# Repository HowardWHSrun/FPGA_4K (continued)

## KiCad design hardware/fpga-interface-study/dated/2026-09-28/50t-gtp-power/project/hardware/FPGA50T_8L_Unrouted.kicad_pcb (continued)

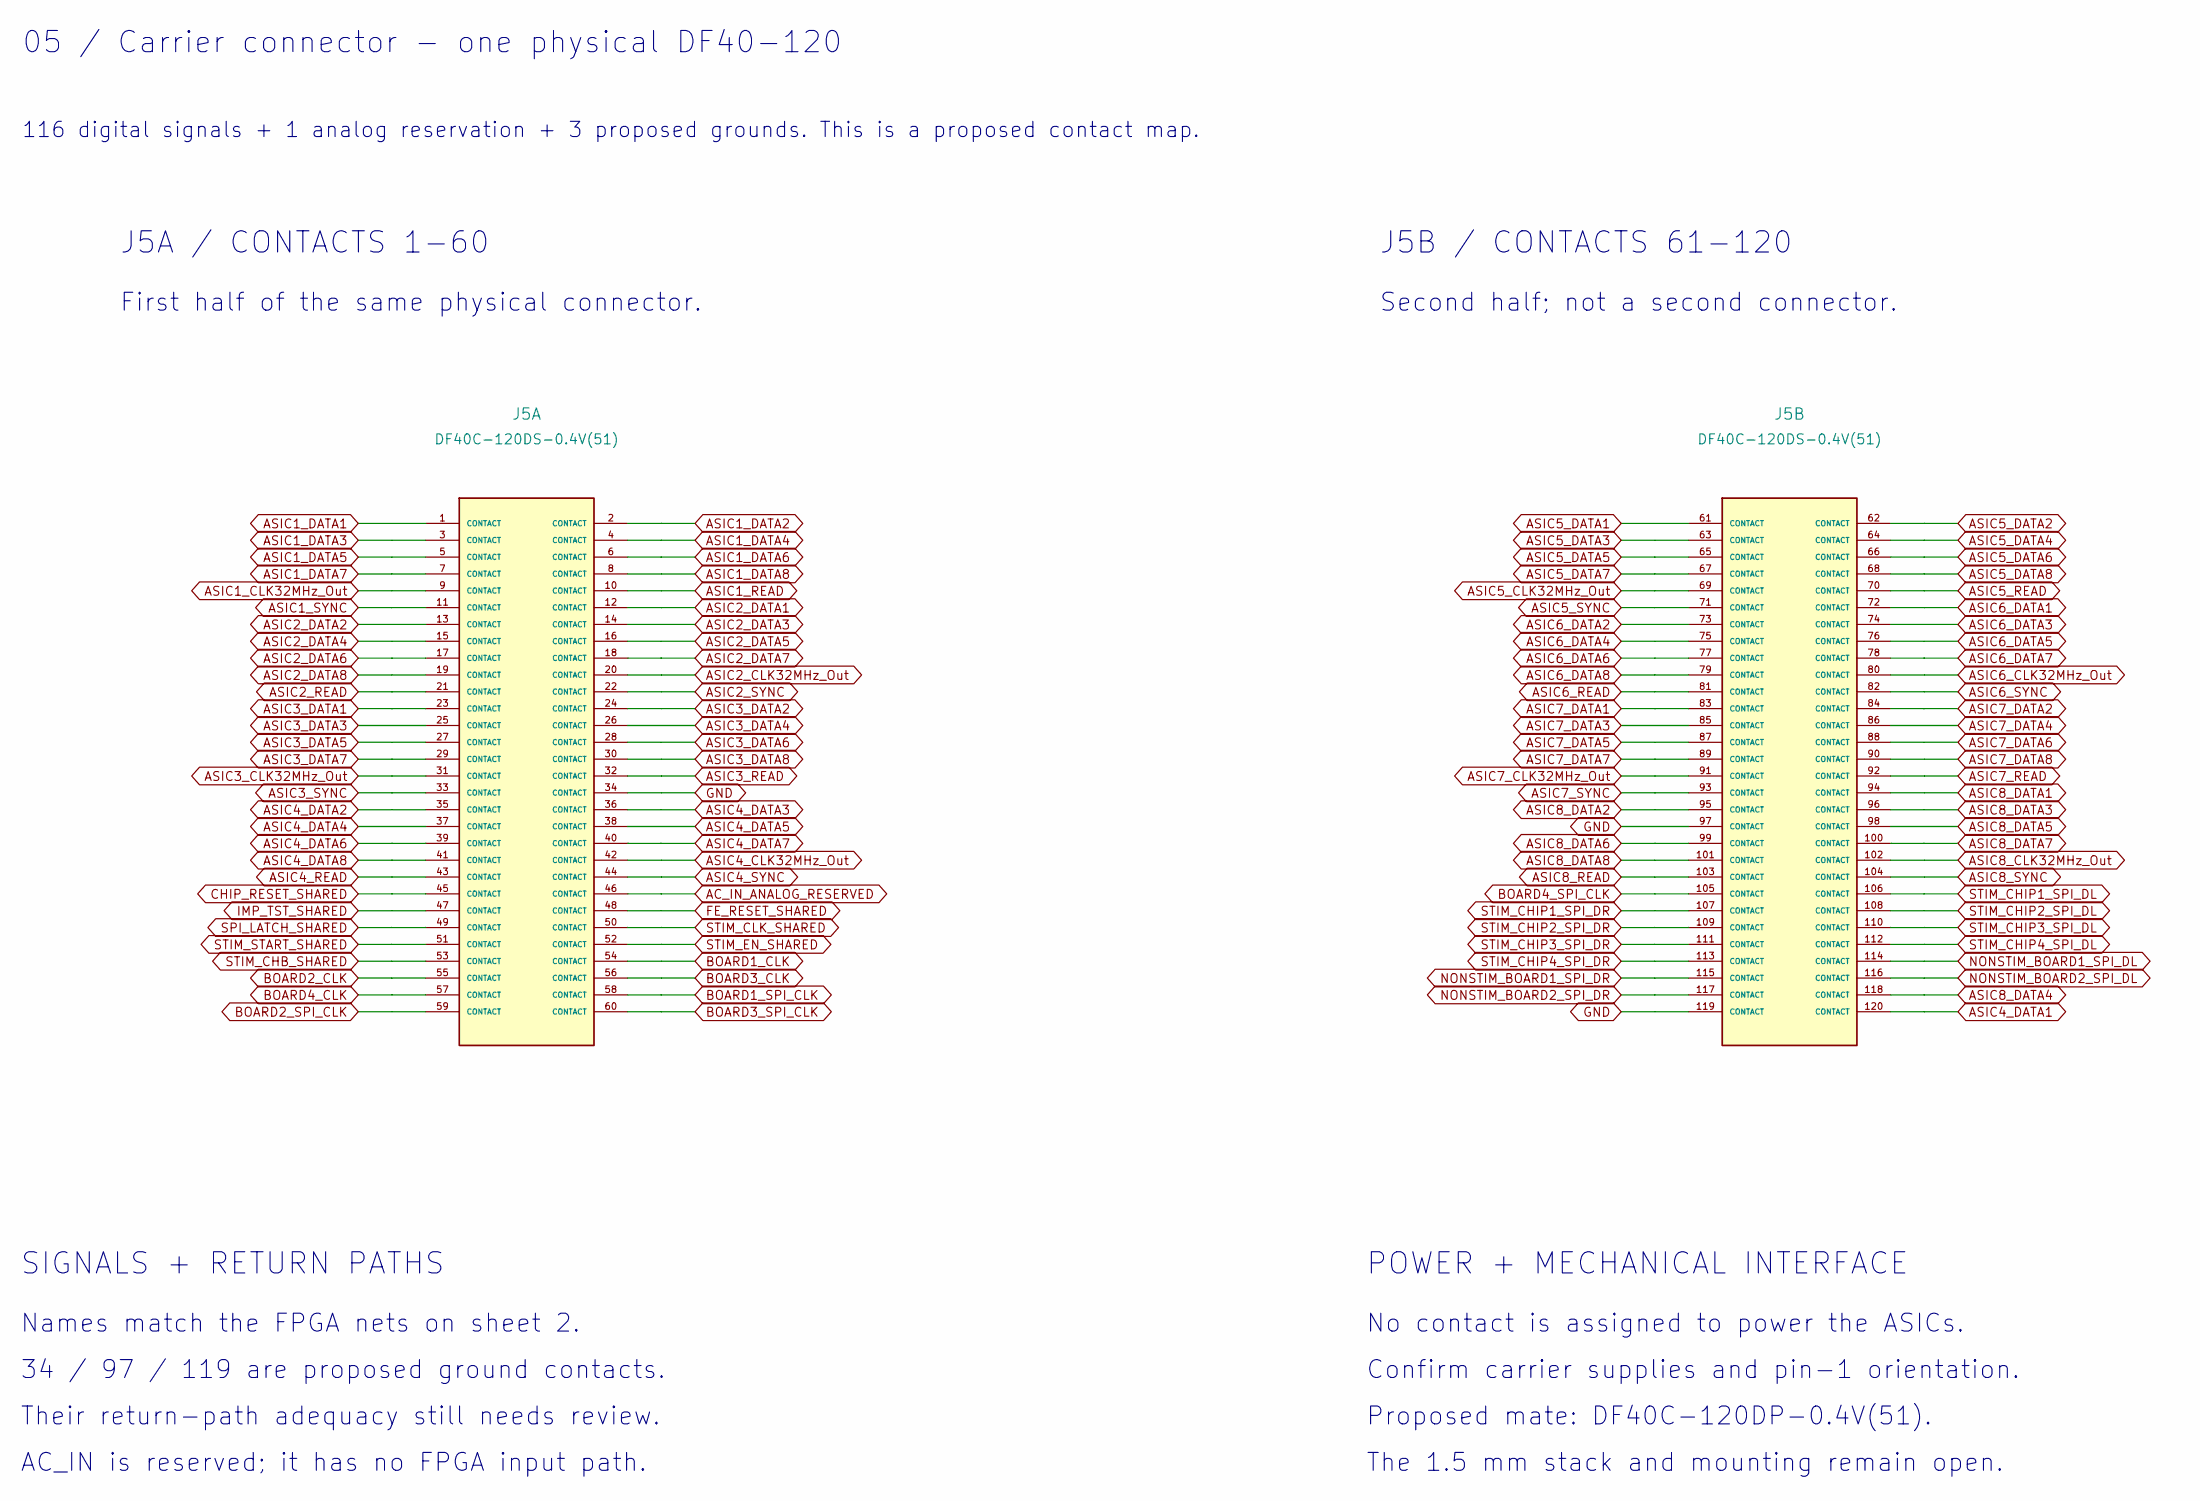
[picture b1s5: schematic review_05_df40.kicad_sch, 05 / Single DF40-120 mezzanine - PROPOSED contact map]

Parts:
J5: DF40C-120DS-0.4V(51); Hirose_DF40C-120DS-0.4V_2x60_P0.4mm; MPN DF40C-120DS-0.4V(51)

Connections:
AC_IN_ANALOG_RESERVED: J5.46
ASIC1_CLK32MHz_Out: J5.9; also elsewhere on the board
ASIC1_DATA1: J5.1; also elsewhere on the board
ASIC1_DATA2: J5.2; also elsewhere on the board
ASIC1_DATA3: J5.3; also elsewhere on the board
ASIC1_DATA4: J5.4; also elsewhere on the board
ASIC1_DATA5: J5.5; also elsewhere on the board
ASIC1_DATA6: J5.6; also elsewhere on the board
ASIC1_DATA7: J5.7; also elsewhere on the board
ASIC1_DATA8: J5.8; also elsewhere on the board
ASIC1_READ: J5.10; also elsewhere on the board
ASIC1_SYNC: J5.11; also elsewhere on the board
ASIC2_CLK32MHz_Out: J5.20; also elsewhere on the board
ASIC2_DATA1: J5.12; also elsewhere on the board
ASIC2_DATA2: J5.13; also elsewhere on the board
ASIC2_DATA3: J5.14; also elsewhere on the board
ASIC2_DATA4: J5.15; also elsewhere on the board
ASIC2_DATA5: J5.16; also elsewhere on the board
ASIC2_DATA6: J5.17; also elsewhere on the board
ASIC2_DATA7: J5.18; also elsewhere on the board
ASIC2_DATA8: J5.19; also elsewhere on the board
ASIC2_READ: J5.21; also elsewhere on the board
ASIC2_SYNC: J5.22; also elsewhere on the board
ASIC3_CLK32MHz_Out: J5.31; also elsewhere on the board
ASIC3_DATA1: J5.23; also elsewhere on the board
ASIC3_DATA2: J5.24; also elsewhere on the board
ASIC3_DATA3: J5.25; also elsewhere on the board
ASIC3_DATA4: J5.26; also elsewhere on the board
ASIC3_DATA5: J5.27; also elsewhere on the board
ASIC3_DATA6: J5.28; also elsewhere on the board
ASIC3_DATA7: J5.29; also elsewhere on the board
ASIC3_DATA8: J5.30; also elsewhere on the board
ASIC3_READ: J5.32; also elsewhere on the board
ASIC3_SYNC: J5.33; also elsewhere on the board
ASIC4_CLK32MHz_Out: J5.42; also elsewhere on the board
ASIC4_DATA1: J5.120; also elsewhere on the board
ASIC4_DATA2: J5.35; also elsewhere on the board
ASIC4_DATA3: J5.36; also elsewhere on the board
ASIC4_DATA4: J5.37; also elsewhere on the board
ASIC4_DATA5: J5.38; also elsewhere on the board
ASIC4_DATA6: J5.39; also elsewhere on the board
ASIC4_DATA7: J5.40; also elsewhere on the board
ASIC4_DATA8: J5.41; also elsewhere on the board
ASIC4_READ: J5.43; also elsewhere on the board
ASIC4_SYNC: J5.44; also elsewhere on the board
ASIC5_CLK32MHz_Out: J5.69; also elsewhere on the board
ASIC5_DATA1: J5.61; also elsewhere on the board
ASIC5_DATA2: J5.62; also elsewhere on the board
ASIC5_DATA3: J5.63; also elsewhere on the board
ASIC5_DATA4: J5.64; also elsewhere on the board
ASIC5_DATA5: J5.65; also elsewhere on the board
ASIC5_DATA6: J5.66; also elsewhere on the board
ASIC5_DATA7: J5.67; also elsewhere on the board
ASIC5_DATA8: J5.68; also elsewhere on the board
ASIC5_READ: J5.70; also elsewhere on the board
ASIC5_SYNC: J5.71; also elsewhere on the board
ASIC6_CLK32MHz_Out: J5.80; also elsewhere on the board
ASIC6_DATA1: J5.72; also elsewhere on the board
ASIC6_DATA2: J5.73; also elsewhere on the board
ASIC6_DATA3: J5.74; also elsewhere on the board
ASIC6_DATA4: J5.75; also elsewhere on the board
ASIC6_DATA5: J5.76; also elsewhere on the board
ASIC6_DATA6: J5.77; also elsewhere on the board
ASIC6_DATA7: J5.78; also elsewhere on the board
ASIC6_DATA8: J5.79; also elsewhere on the board
ASIC6_READ: J5.81; also elsewhere on the board
ASIC6_SYNC: J5.82; also elsewhere on the board
ASIC7_CLK32MHz_Out: J5.91; also elsewhere on the board
ASIC7_DATA1: J5.83; also elsewhere on the board
ASIC7_DATA2: J5.84; also elsewhere on the board
ASIC7_DATA3: J5.85; also elsewhere on the board
ASIC7_DATA4: J5.86; also elsewhere on the board
ASIC7_DATA5: J5.87; also elsewhere on the board
ASIC7_DATA6: J5.88; also elsewhere on the board
ASIC7_DATA7: J5.89; also elsewhere on the board
ASIC7_DATA8: J5.90; also elsewhere on the board
ASIC7_READ: J5.92; also elsewhere on the board
ASIC7_SYNC: J5.93; also elsewhere on the board
ASIC8_CLK32MHz_Out: J5.102; also elsewhere on the board
ASIC8_DATA1: J5.94; also elsewhere on the board
ASIC8_DATA2: J5.95; also elsewhere on the board
ASIC8_DATA3: J5.96; also elsewhere on the board
ASIC8_DATA4: J5.118; also elsewhere on the board
ASIC8_DATA5: J5.98; also elsewhere on the board
ASIC8_DATA6: J5.99; also elsewhere on the board
ASIC8_DATA7: J5.100; also elsewhere on the board
ASIC8_DATA8: J5.101; also elsewhere on the board
ASIC8_READ: J5.103; also elsewhere on the board
ASIC8_SYNC: J5.104; also elsewhere on the board
BOARD1_CLK: J5.54; also elsewhere on the board
BOARD1_SPI_CLK: J5.58; also elsewhere on the board
BOARD2_CLK: J5.55; also elsewhere on the board
BOARD2_SPI_CLK: J5.59; also elsewhere on the board
BOARD3_CLK: J5.56; also elsewhere on the board
BOARD3_SPI_CLK: J5.60; also elsewhere on the board
BOARD4_CLK: J5.57; also elsewhere on the board
BOARD4_SPI_CLK: J5.105; also elsewhere on the board
CHIP_RESET_SHARED: J5.45; also elsewhere on the board
FE_RESET_SHARED: J5.48; also elsewhere on the board
GND: J5.34, J5.97, J5.119; also elsewhere on the board
IMP_TST_SHARED: J5.47; also elsewhere on the board
NONSTIM_BOARD1_SPI_DL: J5.114; also elsewhere on the board
NONSTIM_BOARD1_SPI_DR: J5.115; also elsewhere on the board
NONSTIM_BOARD2_SPI_DL: J5.116; also elsewhere on the board
NONSTIM_BOARD2_SPI_DR: J5.117; also elsewhere on the board
SPI_LATCH_SHARED: J5.49; also elsewhere on the board
STIM_CHB_SHARED: J5.53; also elsewhere on the board
STIM_CHIP1_SPI_DL: J5.106; also elsewhere on the board
STIM_CHIP1_SPI_DR: J5.107; also elsewhere on the board
STIM_CHIP2_SPI_DL: J5.108; also elsewhere on the board
STIM_CHIP2_SPI_DR: J5.109; also elsewhere on the board
STIM_CHIP3_SPI_DL: J5.110; also elsewhere on the board
STIM_CHIP3_SPI_DR: J5.111; also elsewhere on the board
STIM_CHIP4_SPI_DL: J5.112; also elsewhere on the board
STIM_CHIP4_SPI_DR: J5.113; also elsewhere on the board
STIM_CLK_SHARED: J5.50; also elsewhere on the board
STIM_EN_SHARED: J5.52; also elsewhere on the board
STIM_START_SHARED: J5.51; also elsewhere on the board

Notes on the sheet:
05 / Carrier connector - one physical DF40-120
116 digital signals + 1 analog reservation + 3 proposed grounds. This is a proposed contact map.
J5A / CONTACTS 1-60
First half of the same physical connector.
J5B / CONTACTS 61-120
Second half; not a second connector.
SIGNALS + RETURN PATHS
Names match the FPGA nets on sheet 2.
34 / 97 / 119 are proposed ground contacts.
Their return-path adequacy still needs review.
AC_IN is reserved; it has no FPGA input path.
POWER + MECHANICAL INTERFACE
No contact is assigned to power the ASICs.
Confirm carrier supplies and pin-1 orientation.
Proposed mate: DF40C-120DP-0.4V(51).
The 1.5 mm stack and mounting remain open.

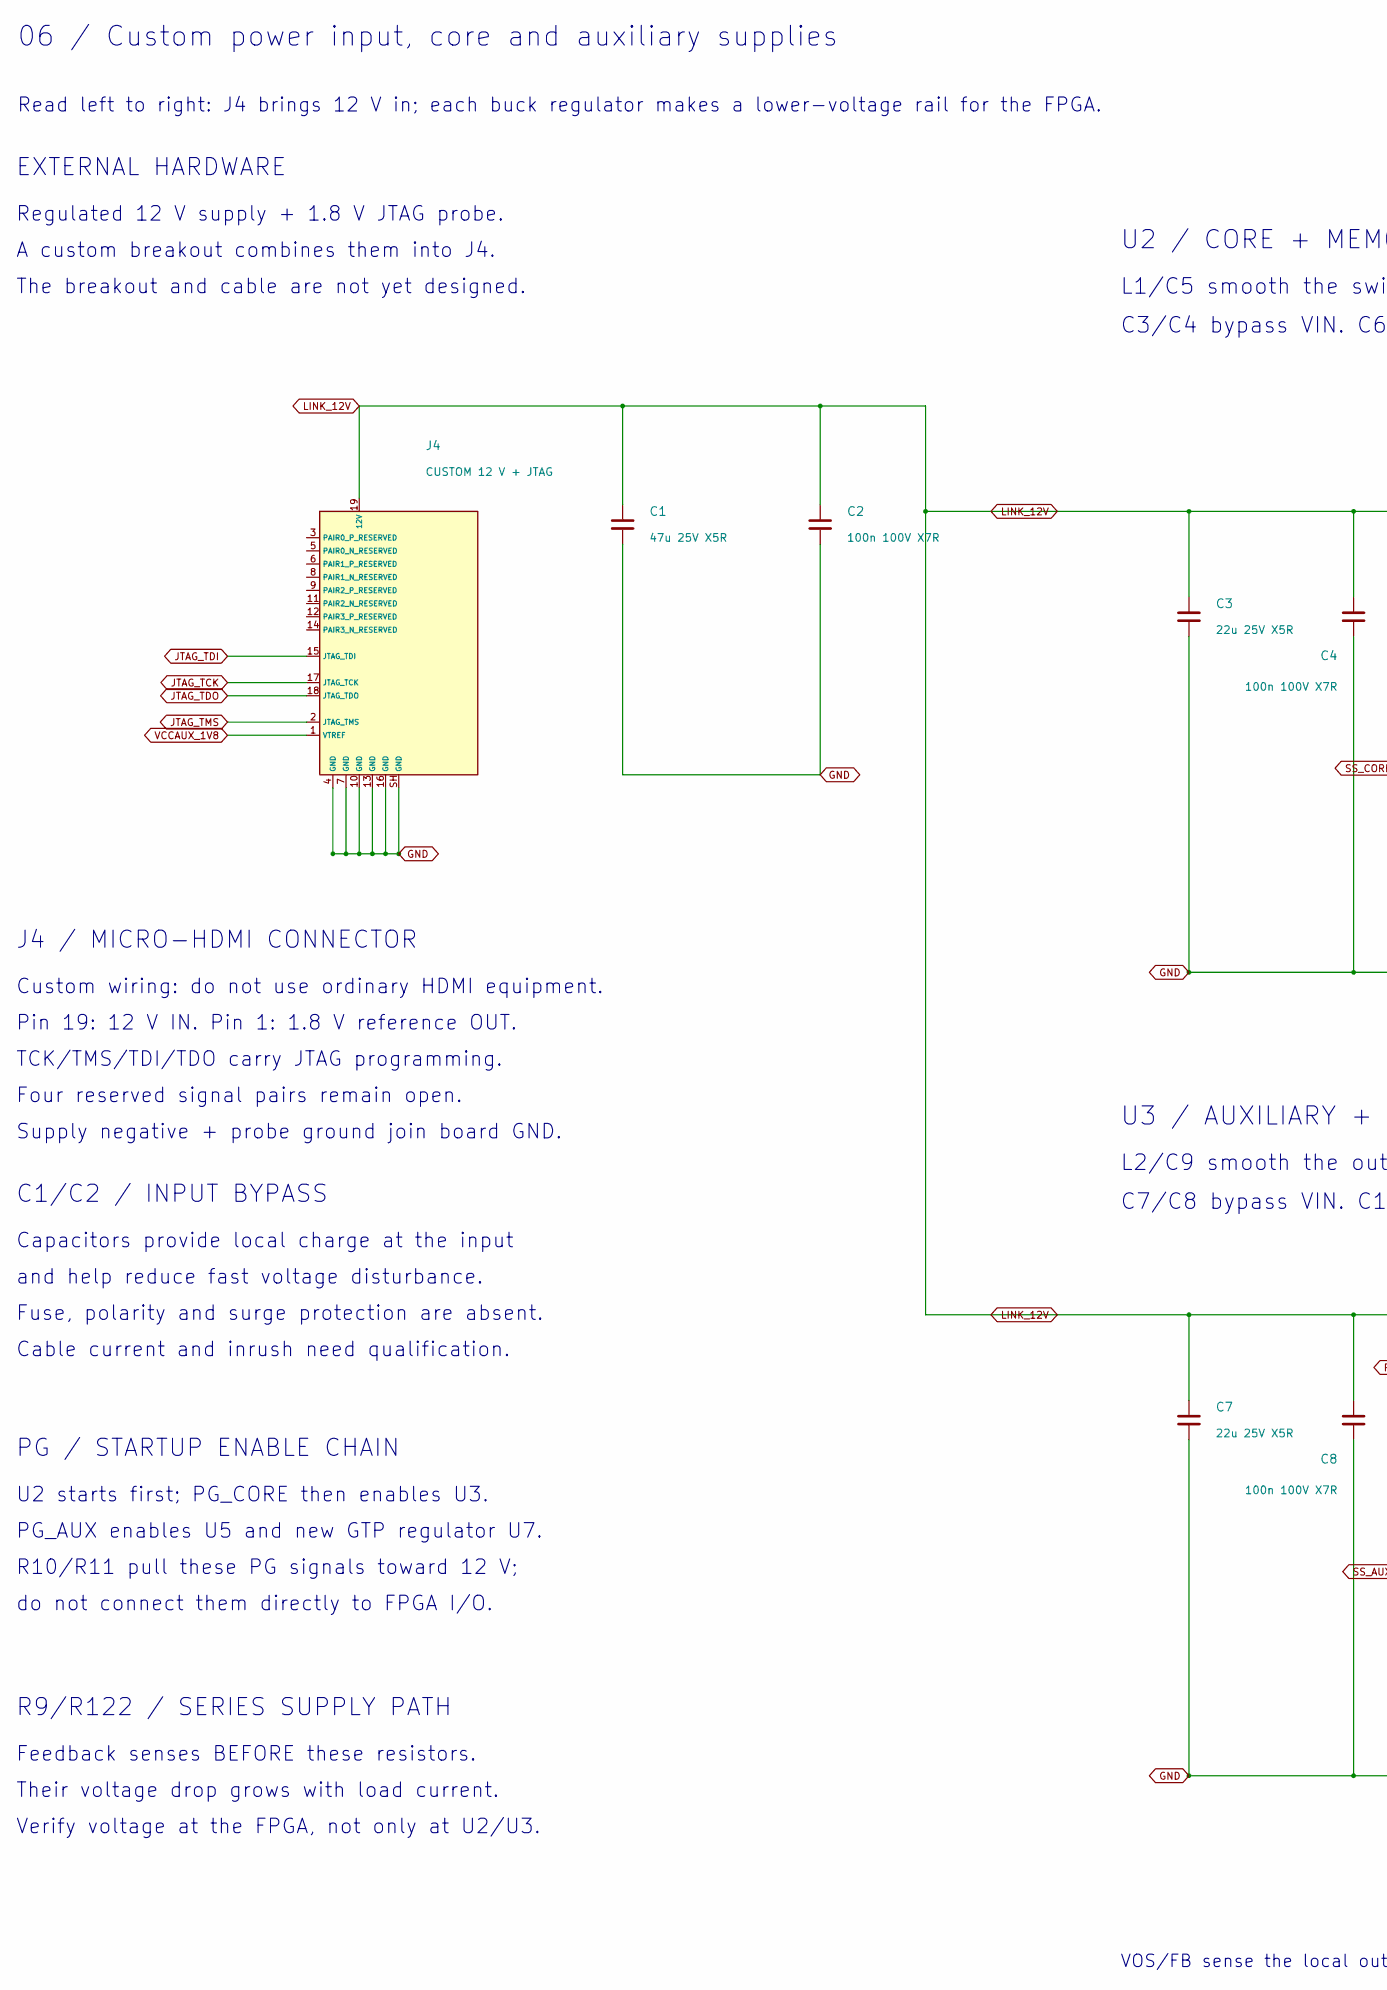
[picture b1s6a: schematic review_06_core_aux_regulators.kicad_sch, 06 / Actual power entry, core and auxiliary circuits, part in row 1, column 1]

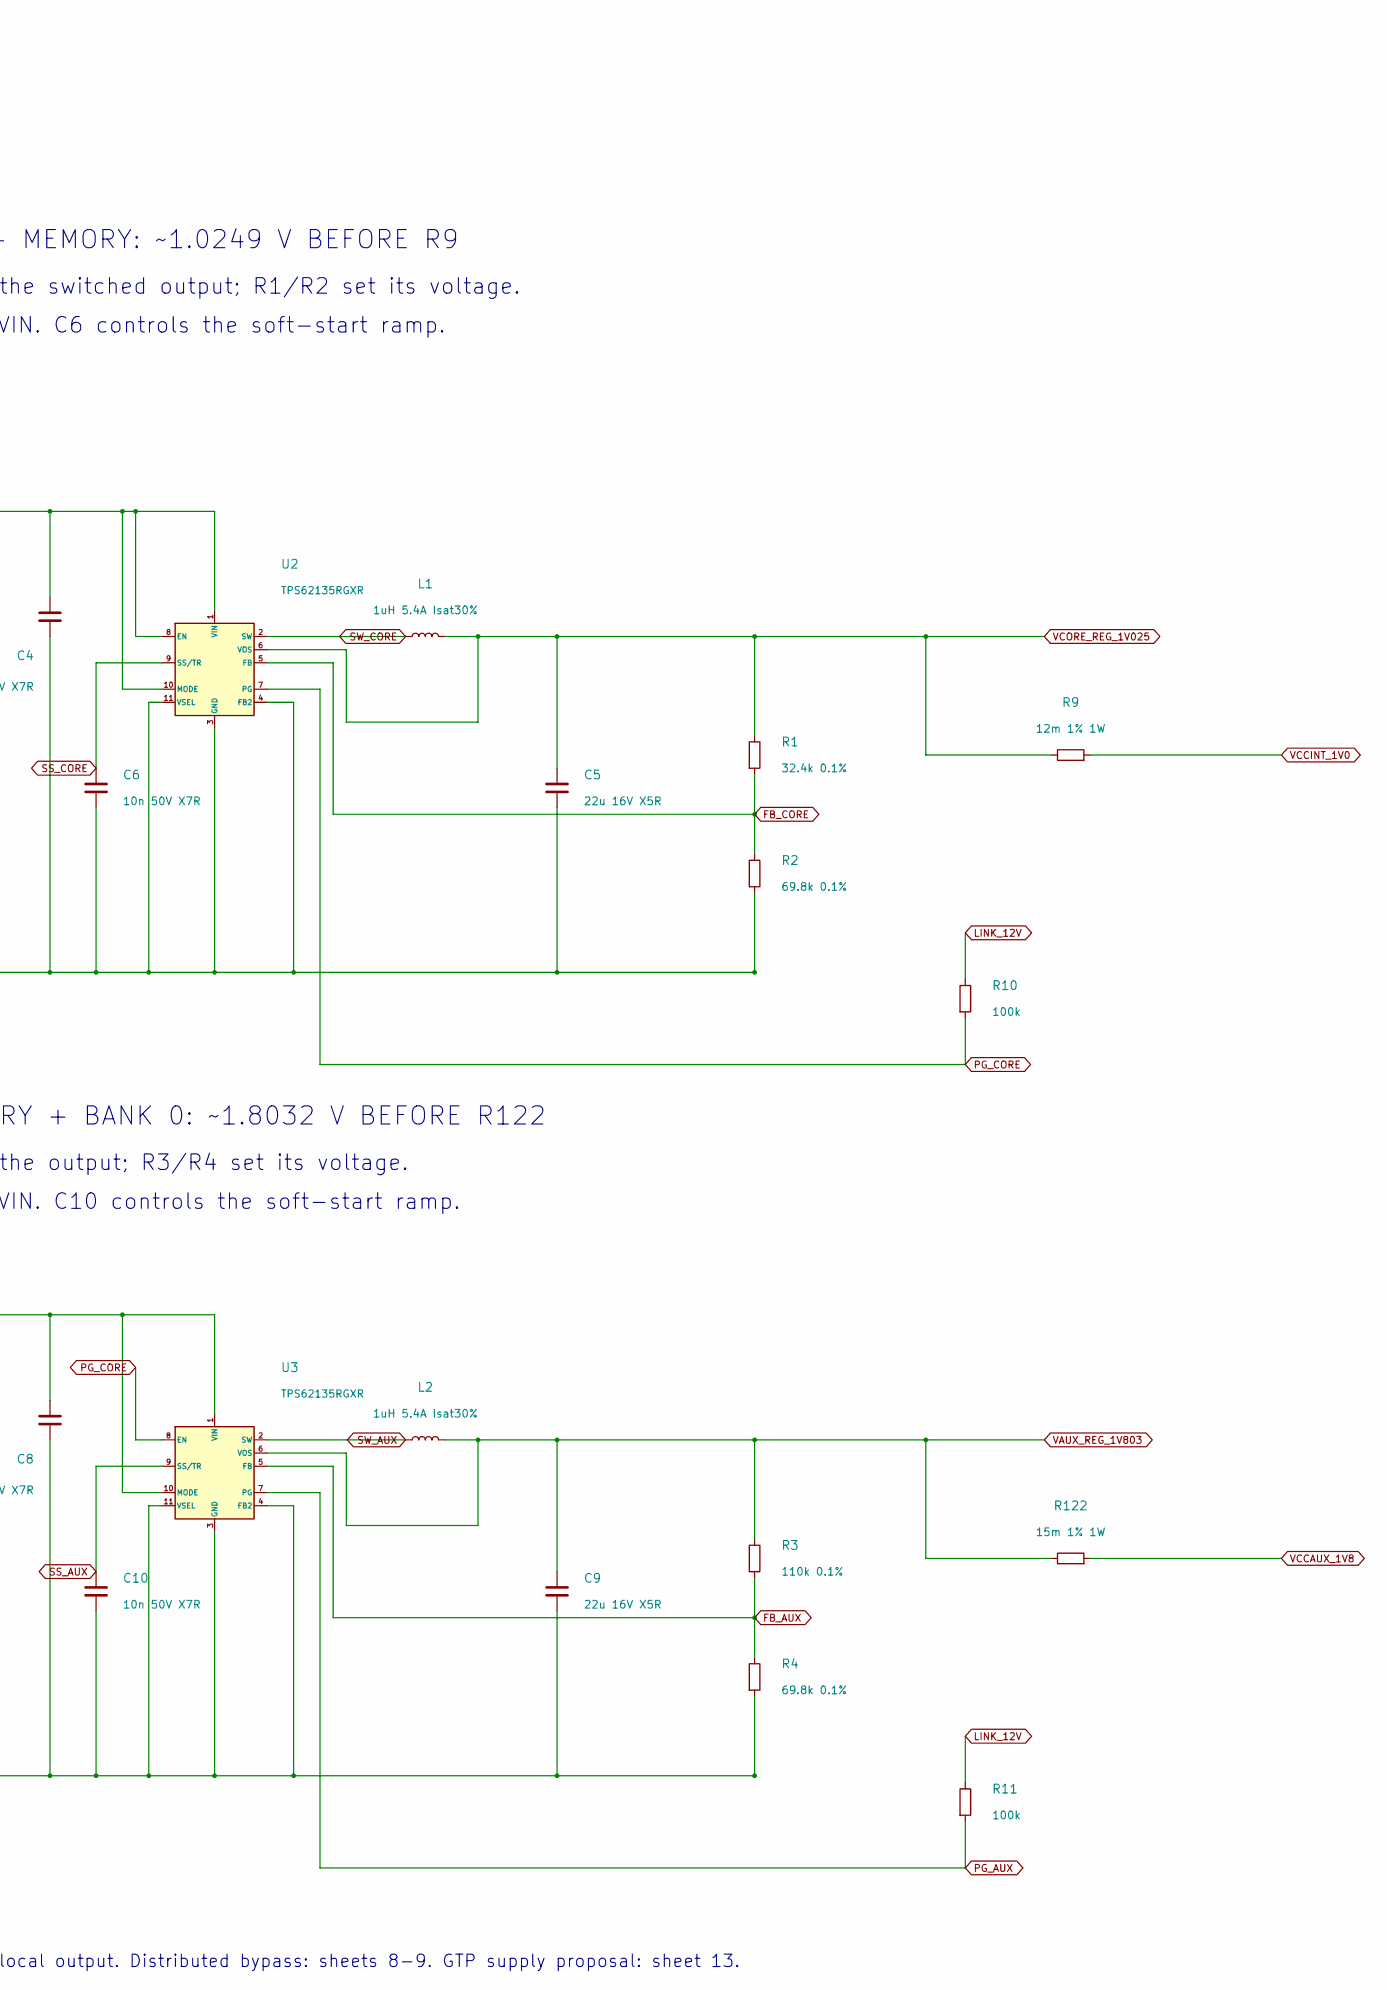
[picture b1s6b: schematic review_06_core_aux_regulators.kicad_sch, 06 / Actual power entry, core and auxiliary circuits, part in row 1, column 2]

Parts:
C1: 47u 25V X5R; Capacitor_SMD__C_1210_3225Metric; MPN MSAST32MAB5476MPNDT1
C2, C4, C8: 100n 100V X7R; Capacitor_SMD__C_0603_1608Metric; MPN GRM188R72A104KA35D
C3, C7: 22u 25V X5R; Capacitor_SMD__C_1206_3216Metric; MPN MSAST31LBB5226MTNA01
C5, C9: 22u 16V X5R; Capacitor_SMD__C_0805_2012Metric; MPN EMK212BBJ226MG-T
C6, C10: 10n 50V X7R; Capacitor_SMD__C_0603_1608Metric; MPN GRM188R71H103KA01D
J4: CUSTOM 12 V + JTAG; LinkPort__MicroHDMI_46765_1xxx; MPN 467651001
L1, L2: 1uH 5.4A Isat30%; PowerDraft__L_Coilcraft_XFL4020; MPN XFL4020-102MEC
R1: 32.4k 0.1%; Resistor_SMD__R_0603_1608Metric; MPN TNPW060332K4BEEA
R2, R4: 69.8k 0.1%; Resistor_SMD__R_0603_1608Metric; MPN TNPW060369K8BEEA
R3: 110k 0.1%; Resistor_SMD__R_0603_1608Metric; MPN TNPW0603110KBEEA
R9: 12m 1% 1W; Resistor_SMD__R_1206_3216Metric; MPN WSLP1206R0120FEA
R10, R11: 100k; Resistor_SMD__R_0603_1608Metric; MPN CRCW0603100KFKEA
R122: 15m 1% 1W; Resistor_SMD__R_1206_3216Metric; MPN WSLP1206R0150FEA
U2, U3: TPS62135RGXR; PowerDraft__Texas_VQFN_RGX0011A_2x3mm; MPN TPS62135RGXR

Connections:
FB_AUX: R3.2, R4.1, U3.5 (FB)
FB_CORE: R1.2, R2.1, U2.5 (FB)
GND: C1.2, C2.2, C3.2, C4.2, C5.2, C6.2, C7.2, C8.2, C9.2, C10.2, J4.4 (GND), J4.7 (GND), J4.10 (GND), J4.13 (GND), J4.16 (GND), J4.SH (GND), R2.2, R4.2, U2.3 (GND), U2.4 (FB2), U2.11 (VSEL), U3.3 (GND), U3.4 (FB2), U3.11 (VSEL); also elsewhere on the board
JTAG_TCK: J4.17 (JTAG_TCK); also elsewhere on the board
JTAG_TDI: J4.15 (JTAG_TDI); also elsewhere on the board
JTAG_TDO: J4.18 (JTAG_TDO); also elsewhere on the board
JTAG_TMS: J4.2 (JTAG_TMS); also elsewhere on the board
LINK_12V: C1.1, C2.1, C3.1, C4.1, C7.1, C8.1, J4.19 (12V), R10.1, R11.1, U2.1 (VIN), U2.8 (EN), U2.10 (MODE), U3.1 (VIN), U3.10 (MODE); also elsewhere on the board
PG_AUX: R11.2, U3.7 (PG); also elsewhere on the board
PG_CORE: R10.2, U2.7 (PG), U3.8 (EN)
SS_AUX: C10.1, U3.9 (SS/TR)
SS_CORE: C6.1, U2.9 (SS/TR)
SW_AUX: L2.1, U3.2 (SW)
SW_CORE: L1.1, U2.2 (SW)
VAUX_REG_1V803: C9.1, L2.2, R3.1, R122.1, U3.6 (VOS)
VCCAUX_1V8: J4.1 (VTREF), R122.2; also elsewhere on the board
VCCINT_1V0: R9.2; also elsewhere on the board
VCORE_REG_1V025: C5.1, L1.2, R1.1, R9.1, U2.6 (VOS)

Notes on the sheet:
06 / Custom power input, core and auxiliary supplies
Read left to right: J4 brings 12 V in; each buck regulator makes a lower-voltage rail for the FPGA.
EXTERNAL HARDWARE
Regulated 12 V supply + 1.8 V JTAG probe.
A custom breakout combines them into J4.
The breakout and cable are not yet designed.
J4 / MICRO-HDMI CONNECTOR
Custom wiring: do not use ordinary HDMI equipment.
Pin 19: 12 V IN. Pin 1: 1.8 V reference OUT.
TCK/TMS/TDI/TDO carry JTAG programming.
Four reserved signal pairs remain open.
Supply negative + probe ground join board GND.
C1/C2 / INPUT BYPASS
Capacitors provide local charge at the input
and help reduce fast voltage disturbance.
Fuse, polarity and surge protection are absent.
Cable current and inrush need qualification.
PG / STARTUP ENABLE CHAIN
U2 starts first; PG_CORE then enables U3.
PG_AUX enables U5 and new GTP regulator U7.
R10/R11 pull these PG signals toward 12 V;
do not connect them directly to FPGA I/O.
R9/R122 / SERIES SUPPLY PATH
Feedback senses BEFORE these resistors.
Their voltage drop grows with load current.
Verify voltage at the FPGA, not only at U2/U3.
U2 / CORE + MEMORY: ~1.0249 V BEFORE R9
L1/C5 smooth the switched output; R1/R2 set its voltage.
C3/C4 bypass VIN. C6 controls the soft-start ramp.
U3 / AUXILIARY + BANK 0: ~1.8032 V BEFORE R122
L2/C9 smooth the output; R3/R4 set its voltage.
C7/C8 bypass VIN. C10 controls the soft-start ramp.
VOS/FB sense the local output. Distributed bypass: sheets 8-9. GTP supply proposal: sheet 13.

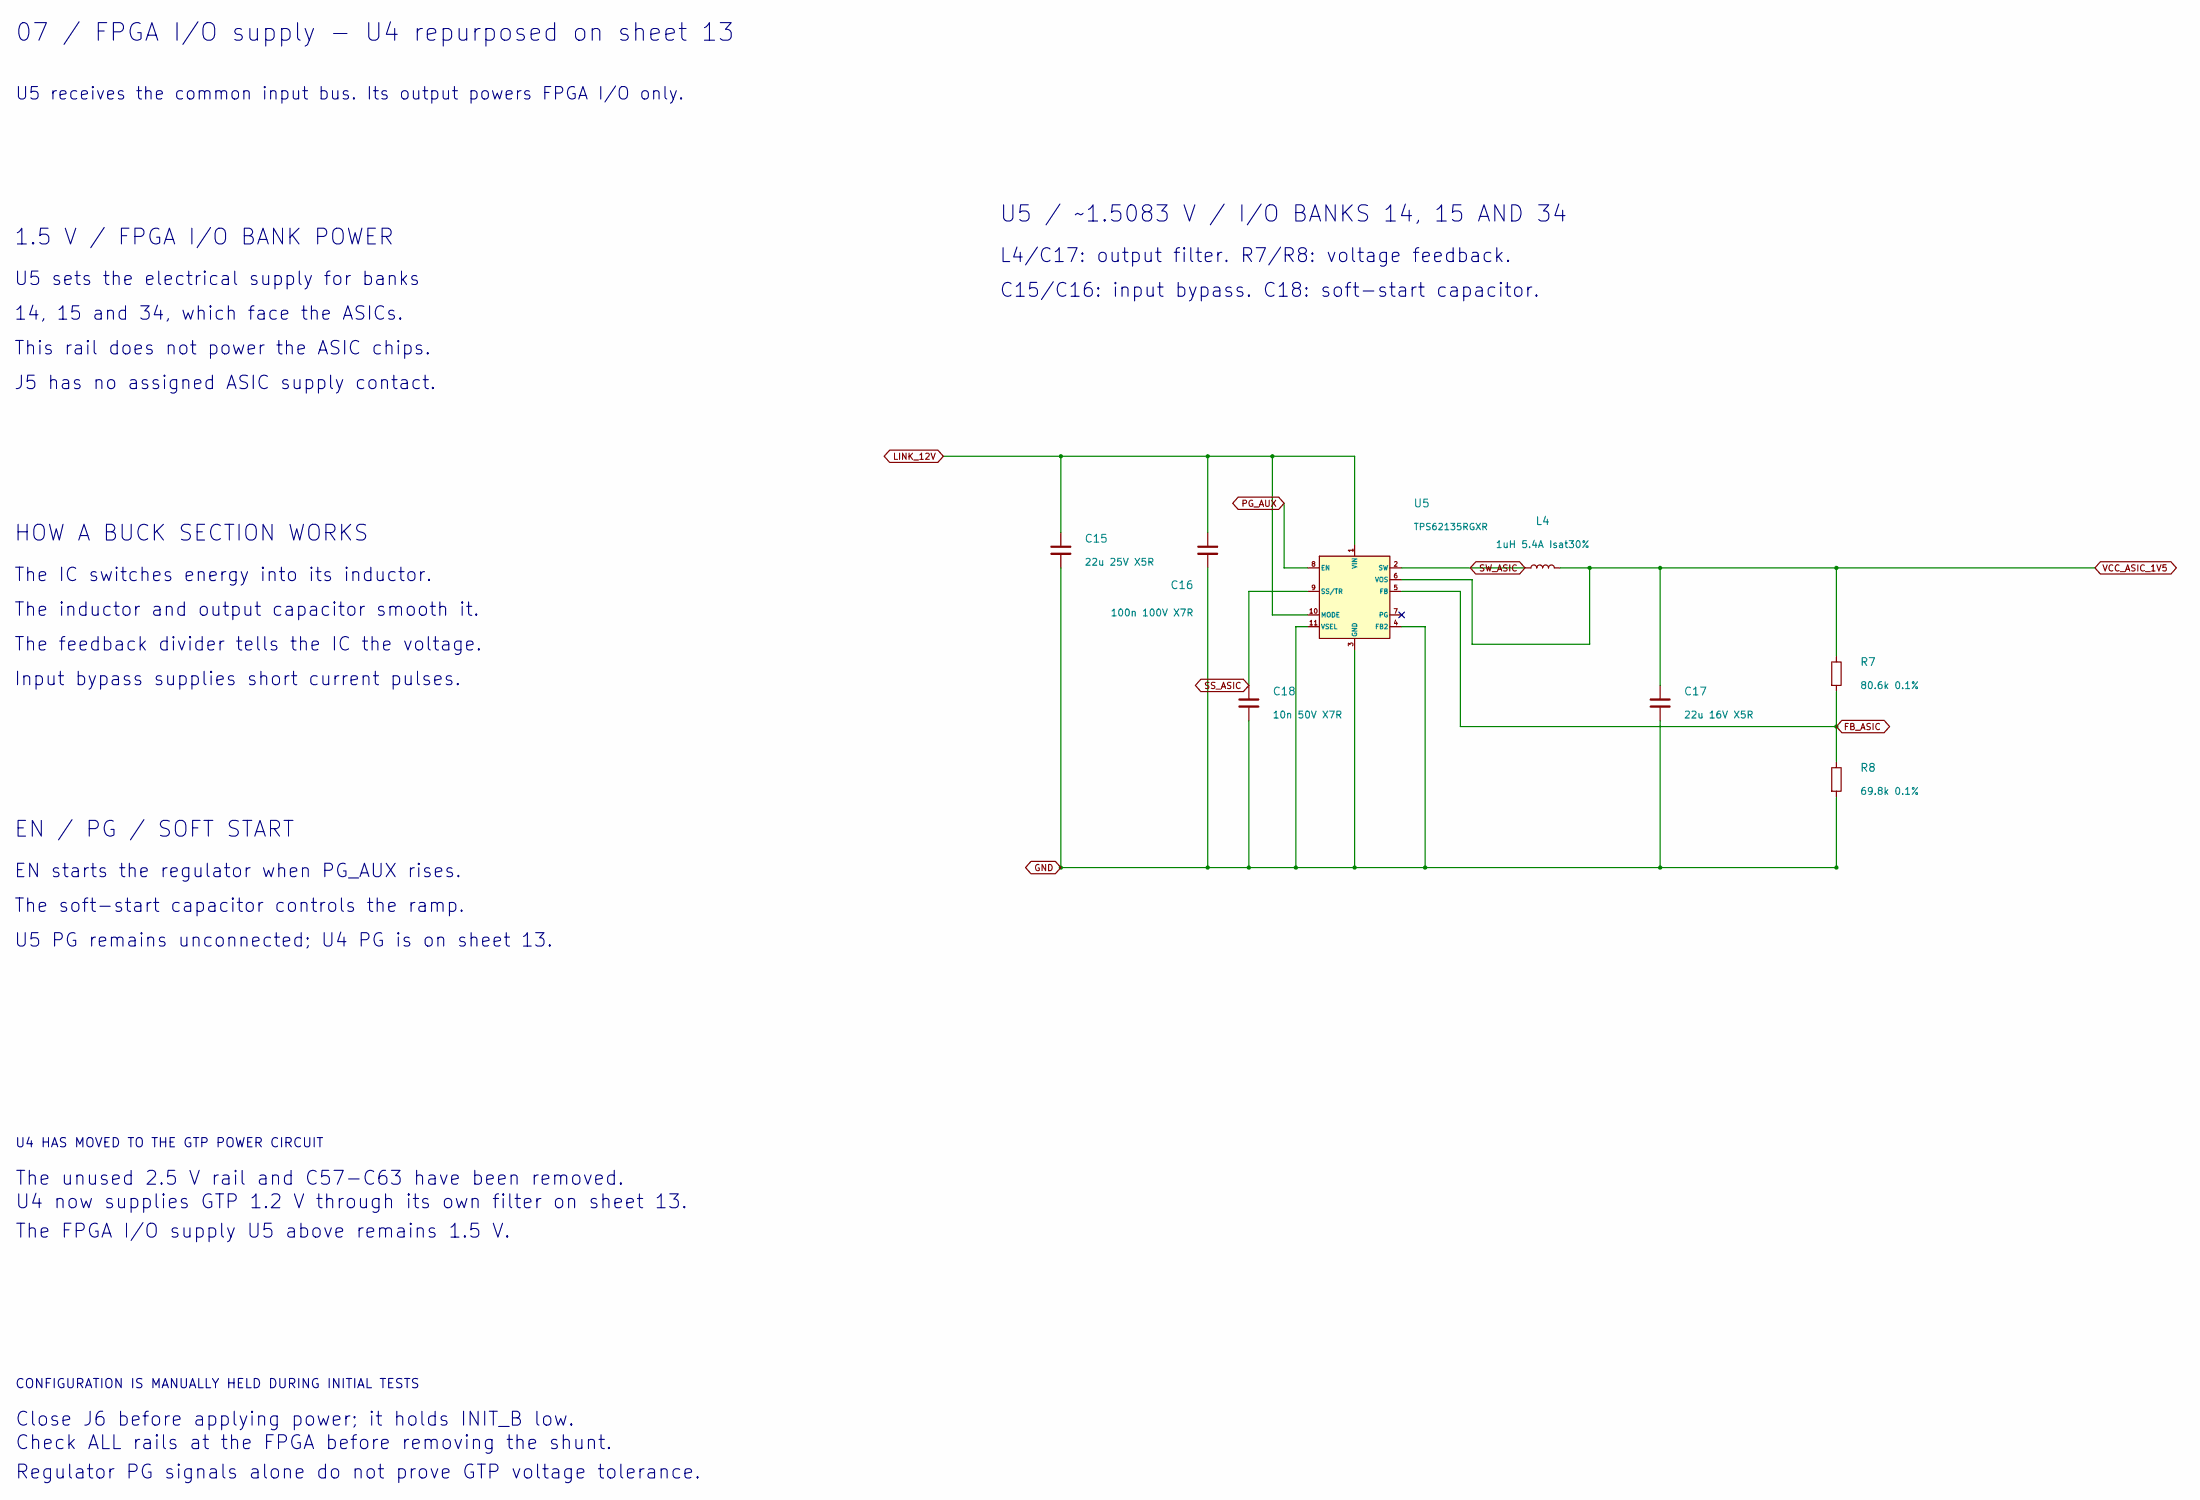
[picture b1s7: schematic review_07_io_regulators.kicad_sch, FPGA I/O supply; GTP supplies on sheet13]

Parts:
C15: 22u 25V X5R; Capacitor_SMD__C_1206_3216Metric; MPN MSAST31LBB5226MTNA01
C16: 100n 100V X7R; Capacitor_SMD__C_0603_1608Metric; MPN GRM188R72A104KA35D
C17: 22u 16V X5R; Capacitor_SMD__C_0805_2012Metric; MPN EMK212BBJ226MG-T
C18: 10n 50V X7R; Capacitor_SMD__C_0603_1608Metric; MPN GRM188R71H103KA01D
L4: 1uH 5.4A Isat30%; PowerDraft__L_Coilcraft_XFL4020; MPN XFL4020-102MEC
R7: 80.6k 0.1%; Resistor_SMD__R_0603_1608Metric; MPN TNPW060380K6BEEA
R8: 69.8k 0.1%; Resistor_SMD__R_0603_1608Metric; MPN TNPW060369K8BEEA
U5: TPS62135RGXR; PowerDraft__Texas_VQFN_RGX0011A_2x3mm; MPN TPS62135RGXR

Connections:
FB_ASIC: R7.2, R8.1, U5.5 (FB)
GND: C15.2, C16.2, C17.2, C18.2, R8.2, U5.3 (GND), U5.4 (FB2), U5.11 (VSEL); also elsewhere on the board
LINK_12V: C15.1, C16.1, U5.1 (VIN), U5.10 (MODE); also elsewhere on the board
PG_AUX: U5.8 (EN); also elsewhere on the board
SS_ASIC: C18.1, U5.9 (SS/TR)
SW_ASIC: L4.1, U5.2 (SW)
VCC_ASIC_1V5: C17.1, L4.2, R7.1, U5.6 (VOS); also elsewhere on the board

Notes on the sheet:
07 / FPGA I/O supply - U4 repurposed on sheet 13
U5 receives the common input bus. Its output powers FPGA I/O only.
1.5 V / FPGA I/O BANK POWER
U5 sets the electrical supply for banks
14, 15 and 34, which face the ASICs.
This rail does not power the ASIC chips.
J5 has no assigned ASIC supply contact.
HOW A BUCK SECTION WORKS
The IC switches energy into its inductor.
The inductor and output capacitor smooth it.
The feedback divider tells the IC the voltage.
Input bypass supplies short current pulses.
EN / PG / SOFT START
EN starts the regulator when PG_AUX rises.
The soft-start capacitor controls the ramp.
U5 PG remains unconnected; U4 PG is on sheet 13.
U5 / ~1.5083 V / I/O BANKS 14, 15 AND 34
L4/C17: output filter. R7/R8: voltage feedback.
C15/C16: input bypass. C18: soft-start capacitor.
U4 HAS MOVED TO THE GTP POWER CIRCUIT
The unused 2.5 V rail and C57-C63 have been removed.
U4 now supplies GTP 1.2 V through its own filter on sheet 13.
The FPGA I/O supply U5 above remains 1.5 V.
CONFIGURATION IS MANUALLY HELD DURING INITIAL TESTS
Close J6 before applying power; it holds INIT_B low.
Check ALL rails at the FPGA before removing the shunt.
Regulator PG signals alone do not prove GTP voltage tolerance.
